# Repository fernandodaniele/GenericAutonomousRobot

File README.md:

# GenericAutonomousRobot (GAR)

Robot móvil diferencial desarrollado por el Grupo 1 para Técnicas Digitales III (TDIII) y Medidas Electrónicas II (MEII). La STM32 controla el movimiento, adquiere los sensores y ejecuta Safety y la navegación. La ESP32 sirve una interfaz web local para operar el robot y consultar su telemetría.

- Control manual, STOP y rearme explícito, con supervisión de proximidad, ausencia de piso y validez de sensores.
- Navegación autónoma supervisada con exploración local, odometría de encoders y maniobras acotadas.
- Panel web sin Internet, con estado, sensores, calibración manual del giroscopio y mapa 2D de ocupación posible.
- Registro de eventos en microSD. Funcionó en pruebas anteriores y requiere una nueva comprobación física por inconvenientes recientes del módulo.

La [arquitectura del sistema](Docs/ARCHITECTURE.md) describe tareas, interfaces, perfiles de navegación y límites de cada subsistema.

## Hardware

| Elemento | Configuración |
|---|---|
| Control | STM32F407G-DISC1, Cortex-M4 a 168 MHz, FreeRTOS |
| Comunicaciones | ESP32 clásico, objetivo `esp32dev` en PlatformIO con ESP-IDF |
| Tracción | Dos motores DC N20 con encoders, driver TB6612FNG |
| Sensores | Dos HC-SR04, frontal y trasero, cuatro TCRT5000 para detectar ausencia de piso y un MPU6050 |
| Registro | microSD por SPI y RTC DS1302 |
| Alimentación del prototipo | Batería LiPo 2S, 7,4 V nominales |

## Repositorio

| Ruta | Contenido |
|---|---|
| [Firmware/stm32_control](Firmware/stm32_control) | Firmware de control, Makefile y pruebas nativas |
| [Firmware/esp32_gateway](Firmware/esp32_gateway) | Firmware de comunicaciones, recursos web embebidos y pruebas |
| [Docs](Docs) | Arquitectura, diagramas del informe y convenciones |
| [Docs/Pruebas](Docs/Pruebas) | Procedimientos y resultados documentados por etapa |
| [Hardware](Hardware) | Lista de componentes y proyecto KiCad |

Abrir [PCB_Robot_Autonomo.kicad_pro](Hardware/PCB_Robot_Autonomo/PCB_Robot_Autonomo.kicad_pro) desde el gestor de KiCad 10. Mantener la estructura de la carpeta para que KiCad resuelva las tablas y modelos locales.

## Compilación y pruebas

Desde la raíz, con GNU Make y la toolchain ARM en el PATH para STM32, y PlatformIO para ESP32:

```sh
make -C Firmware/stm32_control -j4
pio run -d Firmware/esp32_gateway -e esp32
```

En Windows se puede usar `mingw32-make`. El entorno ESP32 fija la plataforma `espressif32 @ 6.12.0` y usa ESP-IDF 5.5.0. PlatformIO genera `firmware.elf` y `firmware.bin` en `Firmware/esp32_gateway/.pio/build/esp32/`. La aplicación debe caber en la partición factory de 1 MiB.

Las siguientes pruebas locales usan GCC nativo y Python 3 para Safety y arranque UART, y Node.js para JavaScript:

```powershell
.\Firmware\stm32_control\Tests\safety_b11\run.bat
.\Firmware\stm32_control\Tests\ultrasound\run.bat
powershell -ExecutionPolicy Bypass -File Firmware/esp32_gateway/Tests/w2/run.ps1
node Firmware/esp32_gateway/Tests/w2/run_js.js
```

Los runners, las fuentes de prueba y los mocks están en [Tests de STM32](Firmware/stm32_control/Tests) y [Tests de ESP32](Firmware/esp32_gateway/Tests). STM32 también dispone de runners para sensores, odometría e IMU. El [workflow de GitHub Actions](.github/workflows/main_ci.yml) compila ambos firmwares en pushes a `master` y pull requests dirigidos a `master`. Las regresiones anteriores se ejecutan por separado.

Para programar ambas placas, consultar el [procedimiento de grabación del firmware](Docs/Pruebas/AUTO3_GIRO_SUPERVISADO.md#programacion-y-validacion-posteriores-requieren-revision-previa).

## Uso y límites

Conectarse a la red local `GenericRobot` y abrir la dirección IP del punto de acceso. El panel distingue la disponibilidad del servidor ESP32 de la comunicación con STM32. Iniciar la exploración requiere una solicitud explícita y supervisión presencial.

La pose es relativa y usa parámetros geométricos provisionales. El mapa estima zonas observadas y posibles obstáculos a partir de ecos y odometría, sin SLAM ni cierre de bucle. Los HC-SR04 no cubren todo el espacio lateral durante un giro, y la falta de eco se trata como dato inválido. Si el teléfono pierde la conexión, STOP remoto puede quedar inaccesible.

## Créditos y licencia

Proyecto académico del Grupo 1. El código del proyecto se distribuye bajo la [licencia MIT](LICENSE), copyright 2026 fernandodaniele. Las bibliotecas incorporadas conservan sus avisos y licencias.

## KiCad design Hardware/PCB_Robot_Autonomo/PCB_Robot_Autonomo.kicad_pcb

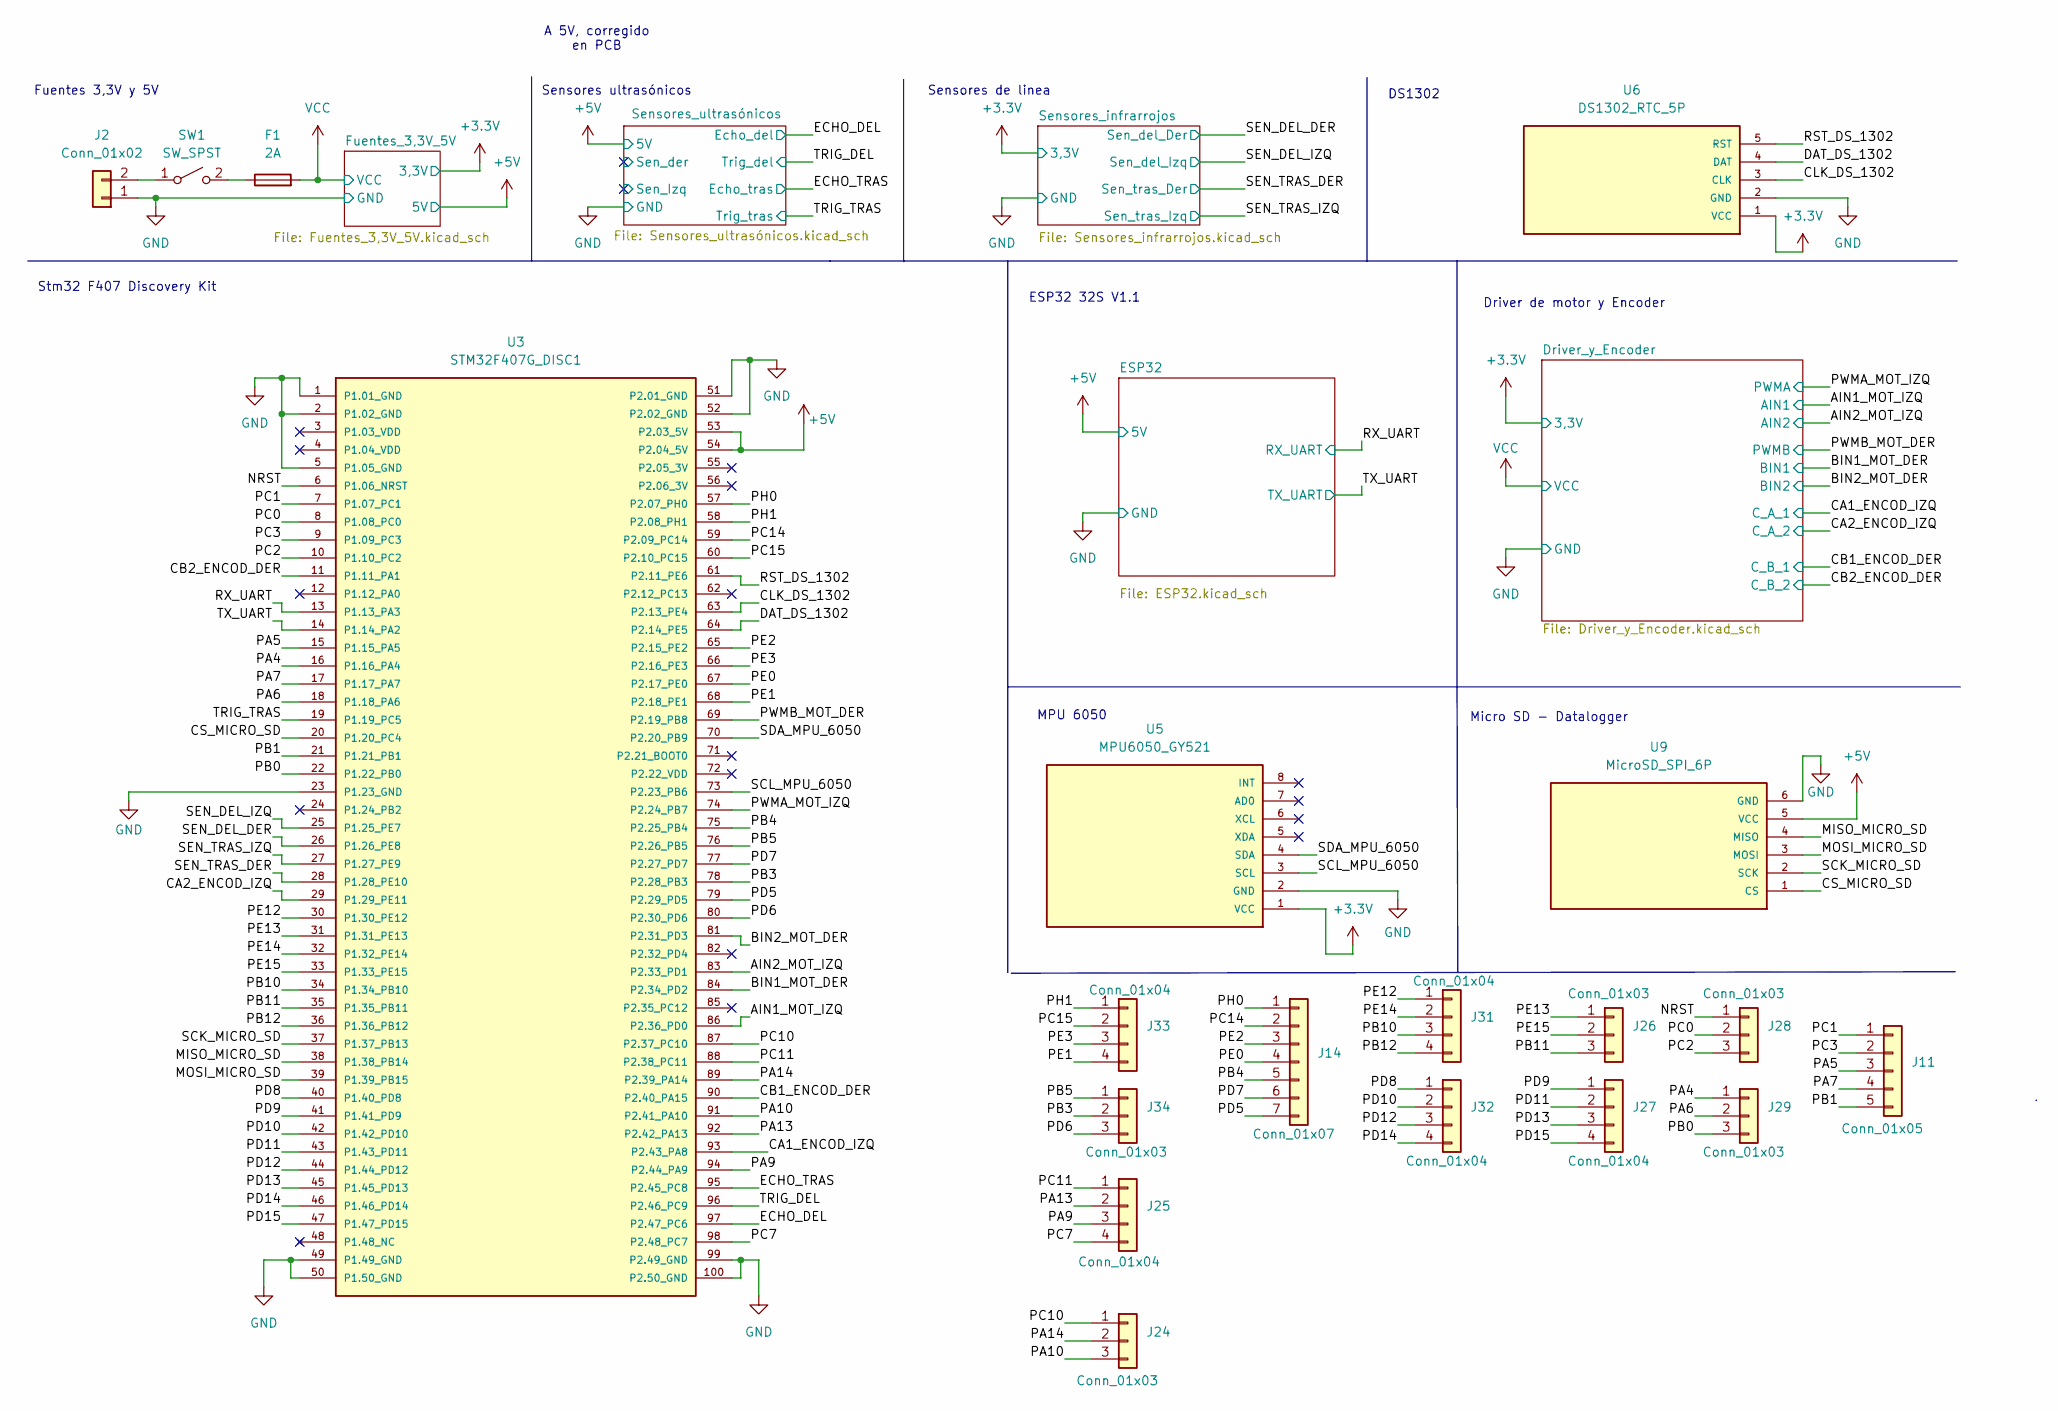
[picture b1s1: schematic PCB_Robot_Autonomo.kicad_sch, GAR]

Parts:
F1: 2A; Fuseholder_Cylinder-5x20mm_Schurter_0031_8201_Horizontal_Op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
J2: Conn_01x02; PinSocket_1x02_P2.54mm_Vertical
J11: Conn_01x05; PinSocket_1x05_P2.54mm_Vertical
J14: Conn_01x07; PinHeader_1x07_P2.54mm_Vertical
J24: Conn_01x03; PinHeader_1x03_P2.54mm_Vertical
J25, J27, J31, J32, J33: Conn_01x04; PinSocket_1x04_P2.54mm_Vertical
J26, J28, J29, J34: Conn_01x03; PinSocket_1x03_P2.54mm_Vertical
SW1: SW_SPST; SW_MTS102_A2_PCB_P4.70mm
U3: STM32F407G_DISC1
U5: MPU6050_GY521
U6: DS1302_RTC_5P
U9: MicroSD_SPI_6P

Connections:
+3.3V: U5.1 (VCC), U6.1 (VCC); also elsewhere on the board
+5V: U3.53 (P2.03_5V), U3.54 (P2.04_5V), U9.5 (VCC); also elsewhere on the board
/AIN1_MOT_IZQ: U3.86 (P2.36_PD0); also elsewhere on the board
/AIN2_MOT_IZQ: U3.83 (P2.33_PD1); also elsewhere on the board
/BIN1_MOT_DER: U3.84 (P2.34_PD2); also elsewhere on the board
/BIN2_MOT_DER: U3.81 (P2.31_PD3); also elsewhere on the board
/CA1_ENCOD_IZQ: U3.93 (P2.43_PA8); also elsewhere on the board
/CA2_ENCOD_IZQ: U3.29 (P1.29_PE11); also elsewhere on the board
/CB1_ENCOD_DER: U3.90 (P2.40_PA15); also elsewhere on the board
/CB2_ENCOD_DER: U3.11 (P1.11_PA1); also elsewhere on the board
/CLK_DS_1302: U3.63 (P2.13_PE4), U6.3 (CLK)
/CS_MICRO_SD: U3.20 (P1.20_PC4), U9.1 (CS)
/DAT_DS_1302: U3.64 (P2.14_PE5), U6.4 (DAT)
/ECHO_DEL: U3.97 (P2.47_PC6); also elsewhere on the board
/ECHO_TRAS: U3.95 (P2.45_PC8); also elsewhere on the board
/MISO_MICRO_SD: U3.38 (P1.38_PB14), U9.4 (MISO)
/MOSI_MICRO_SD: U3.39 (P1.39_PB15), U9.3 (MOSI)
/NRST: J28.1, U3.6 (P1.06_NRST)
/PA4: J29.1, U3.16 (P1.16_PA4)
/PA5: J11.3, U3.15 (P1.15_PA5)
/PA6: J29.2, U3.18 (P1.18_PA6)
/PA7: J11.4, U3.17 (P1.17_PA7)
/PA9: J25.3, U3.94 (P2.44_PA9)
/PA10: J24.3, U3.91 (P2.41_PA10)
/PA13: J25.2, U3.92 (P2.42_PA13)
/PA14: J24.2, U3.89 (P2.39_PA14)
/PB0: J29.3, U3.22 (P1.22_PB0)
/PB1: J11.5, U3.21 (P1.21_PB1)
/PB3: J34.2, U3.78 (P2.28_PB3)
/PB4: J14.5, U3.75 (P2.25_PB4)
/PB5: J34.1, U3.76 (P2.26_PB5)
/PB10: J31.3, U3.34 (P1.34_PB10)
/PB11: J26.3, U3.35 (P1.35_PB11)
/PB12: J31.4, U3.36 (P1.36_PB12)
/PC0: J28.2, U3.8 (P1.08_PC0)
/PC1: J11.1, U3.7 (P1.07_PC1)
/PC2: J28.3, U3.10 (P1.10_PC2)
/PC3: J11.2, U3.9 (P1.09_PC3)
/PC7: J25.4, U3.98 (P2.48_PC7)
/PC10: J24.1, U3.87 (P2.37_PC10)
/PC11: J25.1, U3.88 (P2.38_PC11)
/PC14: J14.2, U3.59 (P2.09_PC14)
/PC15: J33.2, U3.60 (P2.10_PC15)
/PD5: J14.7, U3.79 (P2.29_PD5)
/PD6: J34.3, U3.80 (P2.30_PD6)
/PD7: J14.6, U3.77 (P2.27_PD7)
/PD8: J32.1, U3.40 (P1.40_PD8)
/PD9: J27.1, U3.41 (P1.41_PD9)
/PD10: J32.2, U3.42 (P1.42_PD10)
/PD11: J27.2, U3.43 (P1.43_PD11)
/PD12: J32.3, U3.44 (P1.44_PD12)
/PD13: J27.3, U3.45 (P1.45_PD13)
/PD14: J32.4, U3.46 (P1.46_PD14)
/PD15: J27.4, U3.47 (P1.47_PD15)
/PE0: J14.4, U3.67 (P2.17_PE0)
/PE1: J33.4, U3.68 (P2.18_PE1)
/PE2: J14.3, U3.65 (P2.15_PE2)
/PE3: J33.3, U3.66 (P2.16_PE3)
/PE12: J31.1, U3.30 (P1.30_PE12)
/PE13: J26.1, U3.31 (P1.31_PE13)
/PE14: J31.2, U3.32 (P1.32_PE14)
/PE15: J26.2, U3.33 (P1.33_PE15)
/PH0: J14.1, U3.57 (P2.07_PH0)
/PH1: J33.1, U3.58 (P2.08_PH1)
/PWMA_MOT_IZQ: U3.74 (P2.24_PB7); also elsewhere on the board
/PWMB_MOT_DER: U3.69 (P2.19_PB8); also elsewhere on the board
/RST_DS_1302: U3.61 (P2.11_PE6), U6.5 (RST)
/RX_UART: U3.13 (P1.13_PA3); also elsewhere on the board
/SCK_MICRO_SD: U3.37 (P1.37_PB13), U9.2 (SCK)
/SCL_MPU_6050: U3.73 (P2.23_PB6), U5.3 (SCL)
/SDA_MPU_6050: U3.70 (P2.20_PB9), U5.4 (SDA)
/SEN_DEL_DER: U3.26 (P1.26_PE8); also elsewhere on the board
/SEN_DEL_IZQ: U3.25 (P1.25_PE7); also elsewhere on the board
/SEN_TRAS_DER: U3.28 (P1.28_PE10); also elsewhere on the board
/SEN_TRAS_IZQ: U3.27 (P1.27_PE9); also elsewhere on the board
/TRIG_DEL: U3.96 (P2.46_PC9); also elsewhere on the board
/TRIG_TRAS: U3.19 (P1.19_PC5); also elsewhere on the board
/TX_UART: U3.14 (P1.14_PA2); also elsewhere on the board
GND: J2.1, U3.1 (P1.01_GND), U3.2 (P1.02_GND), U3.5 (P1.05_GND), U3.23 (P1.23_GND), U3.49 (P1.49_GND), U3.50 (P1.50_GND), U3.51 (P2.01_GND), U3.52 (P2.02_GND), U3.99 (P2.49_GND), U3.100 (P2.50_GND), U5.2 (GND), U6.2 (GND), U9.6 (GND); also elsewhere on the board
unnamed: J2.2, SW1.1 (A)
unnamed: F1.1, SW1.2 (B)
VCC: F1.2; also elsewhere on the board

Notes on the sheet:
Stm32 F407 Discovery Kit
Fuentes 3,3V y 5V
A 5V, corregido en PCB
MPU 6050
DS1302
ESP32 32S V1.1
Sensores de linea
Micro SD - Datalogger
Sensores ultrasónicos
Driver de motor y Encoder

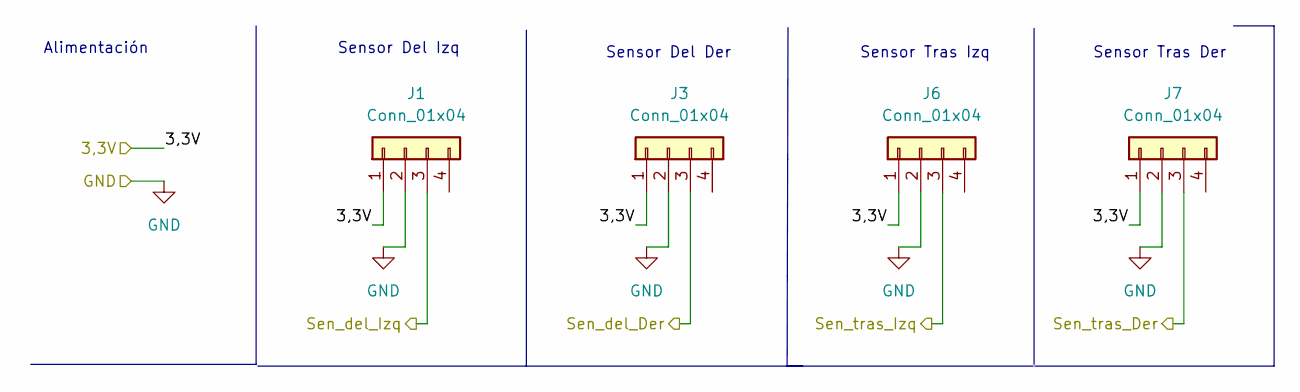
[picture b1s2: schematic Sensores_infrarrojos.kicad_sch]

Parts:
J1: Conn_01x04; PinSocket_1x04_P2.54mm_Vertical
J3, J6, J7: Conn_01x04; PinHeader_1x04_P2.54mm_Vertical

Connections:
+3.3V: J1.1, J3.1, J6.1, J7.1; also elsewhere on the board
/SEN_DEL_DER: J3.3; also elsewhere on the board
/SEN_DEL_IZQ: J1.3; also elsewhere on the board
/SEN_TRAS_DER: J7.3; also elsewhere on the board
/SEN_TRAS_IZQ: J6.3; also elsewhere on the board
GND: J1.2, J3.2, J6.2, J7.2; also elsewhere on the board

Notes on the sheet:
Sensor Tras Der
Sensor Tras Izq
Sensor Del Izq
Sensor Del Der
Alimentación

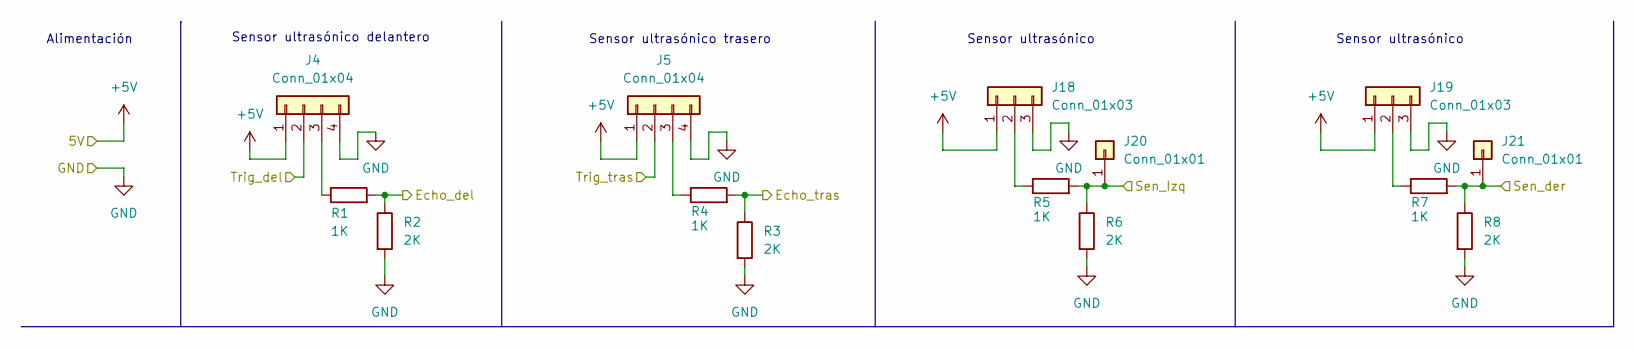
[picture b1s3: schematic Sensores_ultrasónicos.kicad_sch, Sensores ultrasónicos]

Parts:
J4, J5: Conn_01x04; PinHeader_1x04_P2.54mm_Vertical
J18, J19: Conn_01x03; PinHeader_1x03_P2.54mm_Vertical
J20, J21: Conn_01x01; PinHeader_1x01_P2.54mm_Vertical
R1, R4, R5, R7: 1K; R_Axial_DIN0207_L6.3mm_D2.5mm_P10.16mm_Horizontal
R2, R3, R6, R8: 2K; R_Axial_DIN0207_L6.3mm_D2.5mm_P10.16mm_Horizontal

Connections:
+3.3V: J4.1, J5.1, J18.1, J19.1; also elsewhere on the board
/ECHO_DEL: R1.2, R2.1; also elsewhere on the board
/ECHO_TRAS: R3.1, R4.2; also elsewhere on the board
/Sensores_ultrasónicos/Sen_Izq: J20.1 (Pin_1_1), R5.2, R6.1
/Sensores_ultrasónicos/Sen_der: J21.1 (Pin_1_1), R7.2, R8.1
/TRIG_DEL: J4.2; also elsewhere on the board
/TRIG_TRAS: J5.2; also elsewhere on the board
GND: J4.4, J5.4, J18.3, J19.3, R2.2, R3.2, R6.2, R8.2; also elsewhere on the board
unnamed: J4.3, R1.1
unnamed: J5.3, R4.1
unnamed: J18.2, R5.1
unnamed: J19.2, R7.1

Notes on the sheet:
Sensor ultrasónico
Sensor ultrasónico delantero
Sensor ultrasónico trasero
Alimentación
Sensor ultrasónico

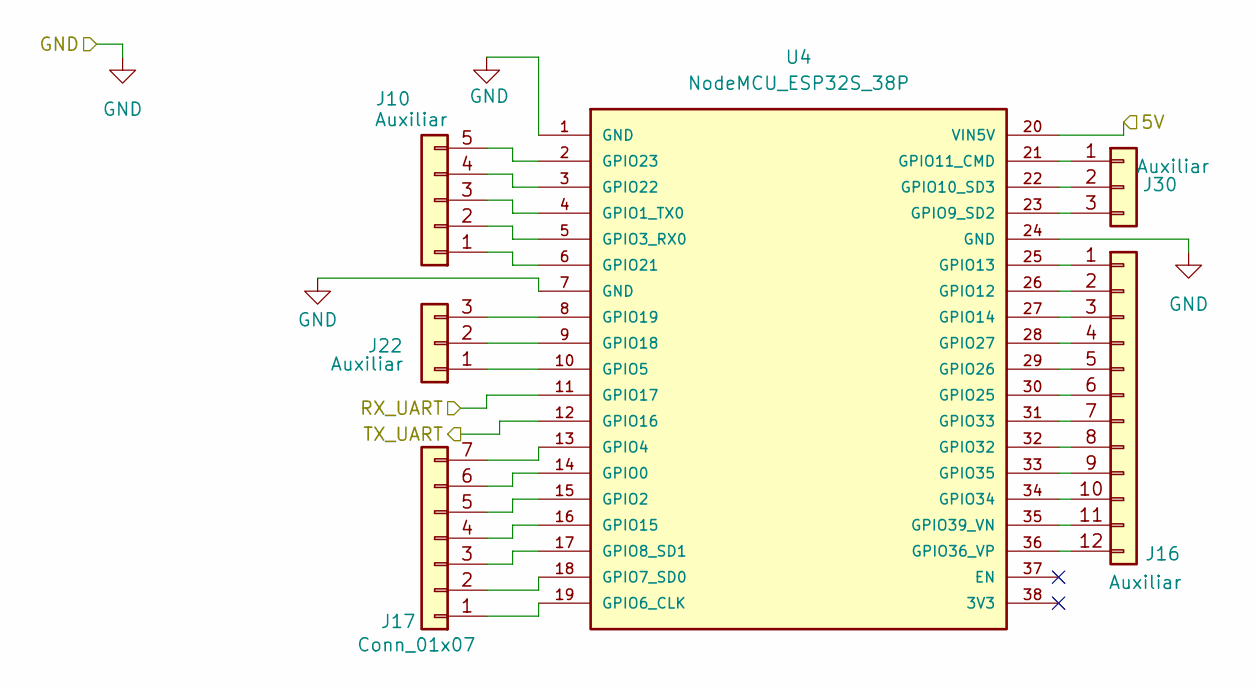
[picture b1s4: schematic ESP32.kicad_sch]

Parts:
J10: Auxiliar; PinHeader_1x05_P2.54mm_Vertical
J16: Auxiliar; PinHeader_1x12_P2.54mm_Vertical
J17: Conn_01x07; PinHeader_1x07_P2.54mm_Vertical
J22, J30: Auxiliar; PinHeader_1x03_P2.54mm_Vertical
U4: NodeMCU_ESP32S_38P

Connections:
+5V: U4.20 (VIN5V); also elsewhere on the board
/RX_UART: U4.11 (GPIO17); also elsewhere on the board
/TX_UART: U4.12 (GPIO16); also elsewhere on the board
GND: U4.1 (GND), U4.7 (GND), U4.24 (GND); also elsewhere on the board
unnamed: J10.1, U4.6 (GPIO21)
unnamed: J10.2, U4.5 (GPIO3_RX0)
unnamed: J10.3, U4.4 (GPIO1_TX0)
unnamed: J10.4, U4.3 (GPIO22)
unnamed: J10.5, U4.2 (GPIO23)
unnamed: J16.1, U4.25 (GPIO13)
unnamed: J16.2, U4.26 (GPIO12)
unnamed: J16.3, U4.27 (GPIO14)
unnamed: J16.4, U4.28 (GPIO27)
unnamed: J16.5, U4.29 (GPIO26)
unnamed: J16.6, U4.30 (GPIO25)
unnamed: J16.7, U4.31 (GPIO33)
unnamed: J16.8, U4.32 (GPIO32)
unnamed: J16.9, U4.33 (GPIO35)
unnamed: J16.10, U4.34 (GPIO34)
unnamed: J16.11, U4.35 (GPIO39_VN)
unnamed: J16.12, U4.36 (GPIO36_VP)
unnamed: J17.1, U4.19 (GPIO6_CLK)
unnamed: J17.2, U4.18 (GPIO7_SD0)
unnamed: J17.3, U4.17 (GPIO8_SD1)
unnamed: J17.4, U4.16 (GPIO15)
unnamed: J17.5, U4.15 (GPIO2)
unnamed: J17.6, U4.14 (GPIO0)
unnamed: J17.7, U4.13 (GPIO4)
unnamed: J22.1, U4.10 (GPIO5)
unnamed: J22.2, U4.9 (GPIO18)
unnamed: J22.3, U4.8 (GPIO19)
unnamed: J30.1, U4.21 (GPIO11_CMD)
unnamed: J30.2, U4.22 (GPIO10_SD3)
unnamed: J30.3, U4.23 (GPIO9_SD2)

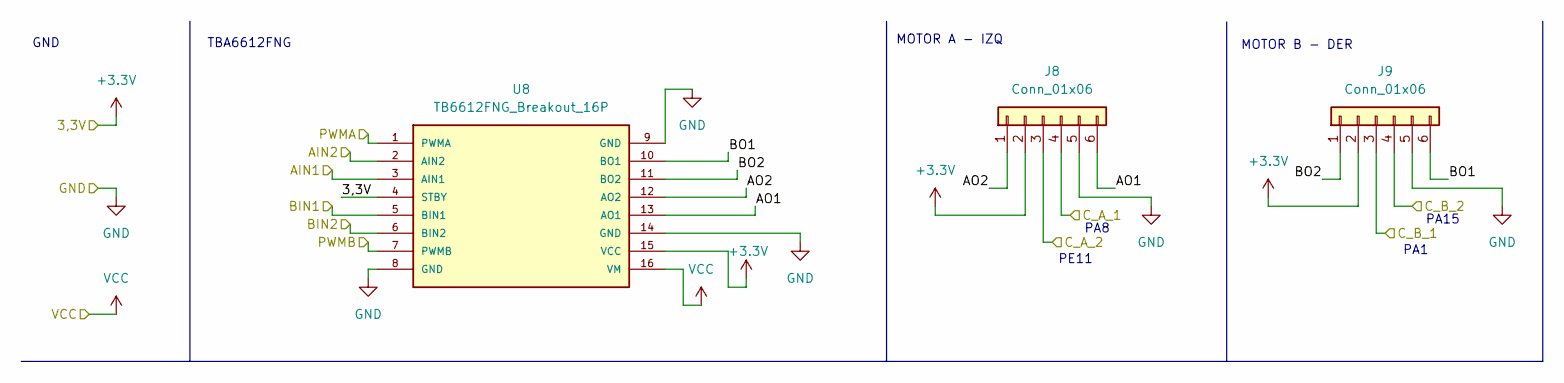
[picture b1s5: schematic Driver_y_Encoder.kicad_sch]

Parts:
J8, J9: Conn_01x06; PinHeader_1x06_P2.54mm_Vertical
U8: TB6612FNG_Breakout_16P

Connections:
+3.3V: J8.2, J9.2, U8.4 (STBY), U8.15 (VCC); also elsewhere on the board
/AIN1_MOT_IZQ: U8.3 (AIN1); also elsewhere on the board
/AIN2_MOT_IZQ: U8.2 (AIN2); also elsewhere on the board
/BIN1_MOT_DER: U8.5 (BIN1); also elsewhere on the board
/BIN2_MOT_DER: U8.6 (BIN2); also elsewhere on the board
/CA1_ENCOD_IZQ: J8.4; also elsewhere on the board
/CA2_ENCOD_IZQ: J8.3; also elsewhere on the board
/CB1_ENCOD_DER: J9.3; also elsewhere on the board
/CB2_ENCOD_DER: J9.4; also elsewhere on the board
/Driver_y_Encoder/AO1: J8.6, U8.13 (AO1)
/Driver_y_Encoder/AO2: J8.1, U8.12 (AO2)
/Driver_y_Encoder/BO1: J9.6, U8.10 (BO1)
/Driver_y_Encoder/BO2: J9.1, U8.11 (BO2)
/PWMA_MOT_IZQ: U8.1 (PWMA); also elsewhere on the board
/PWMB_MOT_DER: U8.7 (PWMB); also elsewhere on the board
GND: J8.5, J9.5, U8.8 (GND), U8.9 (GND), U8.14 (GND); also elsewhere on the board
VCC: U8.16 (VM); also elsewhere on the board

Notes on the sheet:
MOTOR A - IZQ
MOTOR B - DER
PA15
PA1
PA8
GND
PE11
TBA6612FNG

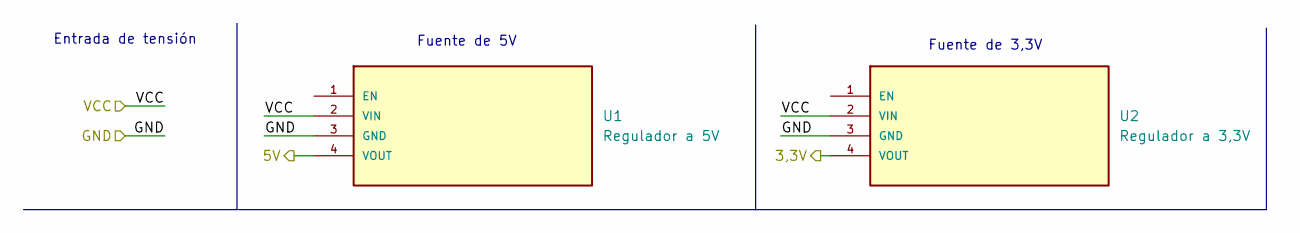
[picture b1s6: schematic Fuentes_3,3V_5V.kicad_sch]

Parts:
U1: Regulador a 5V; StepDown_Mini_3A_0V8_17V
U2: Regulador a 3,3V; StepDown_Mini_3A_0V8_17V

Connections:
+3.3V: U2.4 (VOUT); also elsewhere on the board
+5V: U1.4 (VOUT); also elsewhere on the board
GND: U1.3 (GND), U2.3 (GND); also elsewhere on the board
VCC: U1.2 (VIN), U2.2 (VIN); also elsewhere on the board

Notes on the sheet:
Fuente de 5V
Fuente de 3,3V
Entrada de tensión

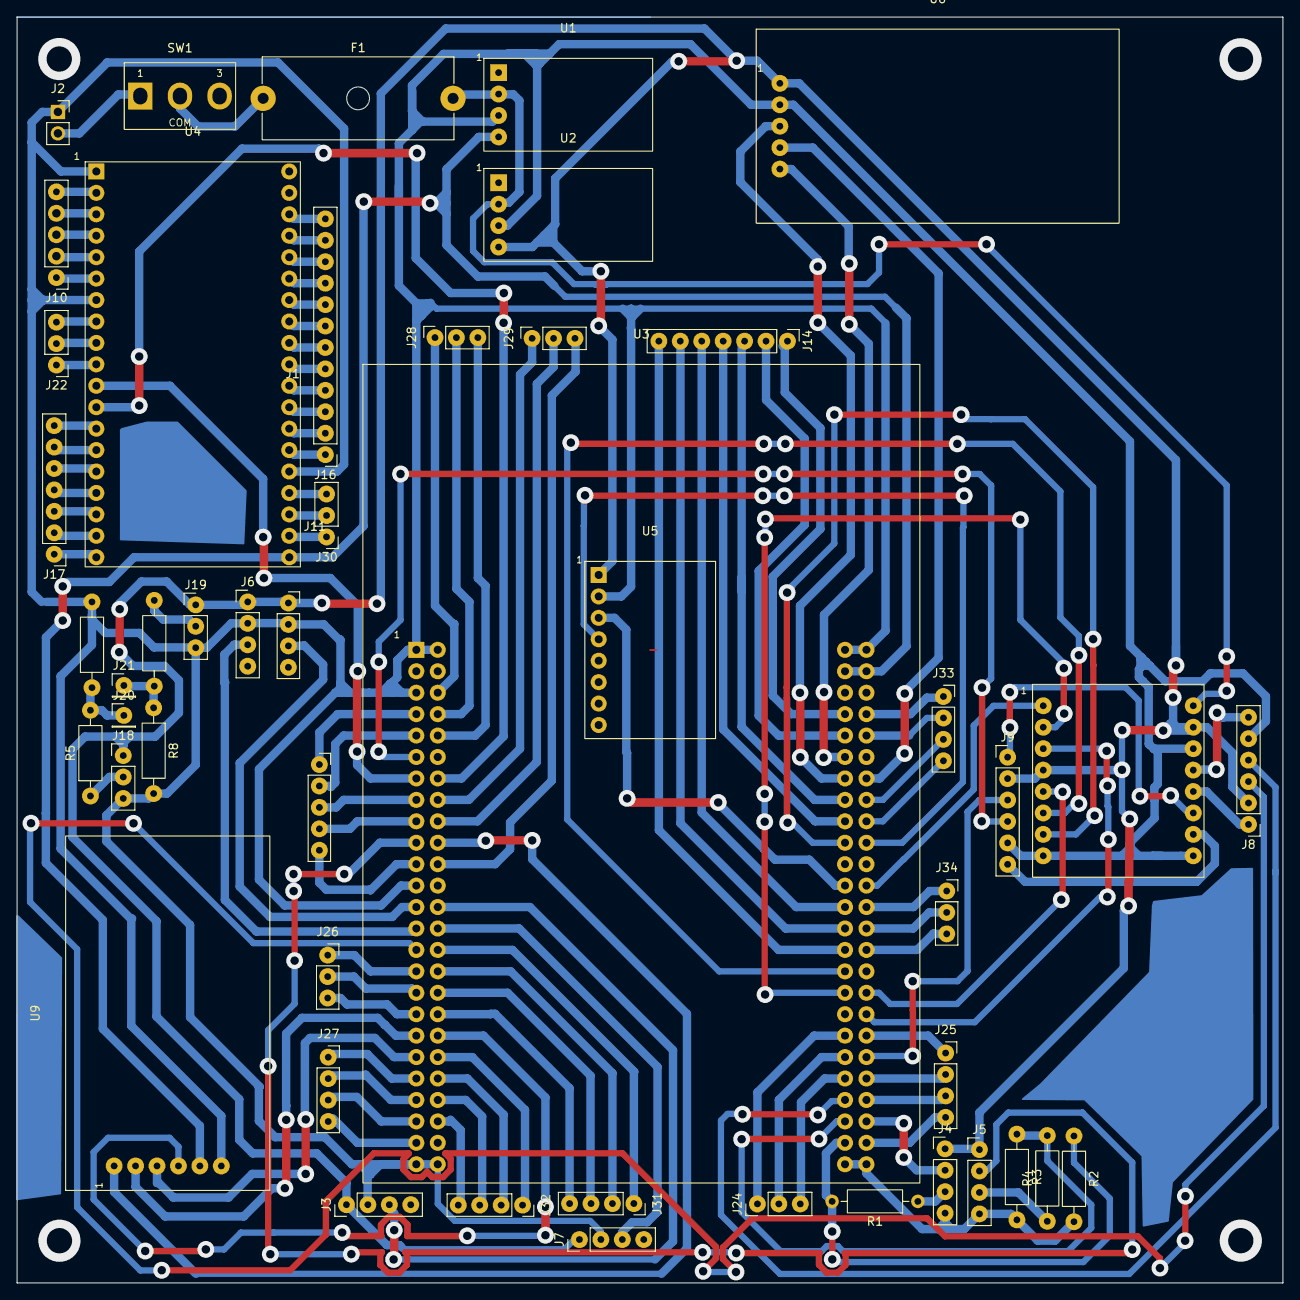
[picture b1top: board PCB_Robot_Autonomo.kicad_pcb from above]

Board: 2 copper layers, 150.0 x 150.0 mm, 48 parts (0 on the bottom side), 122 nets.

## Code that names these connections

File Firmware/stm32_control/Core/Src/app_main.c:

/**
 * @file    app_main.c
 * @brief   Punto de entrada de la aplicación (int main).
 *
 * STM32CubeMX (projectgenerator 4.7.0-B52) NO genera la función main() para
 * este proyecto: su Core/Src/main.c sale SIN main() en cada "Generate Code"
 * (probado 3 veces, incluso borrando main.c antes de regenerar).
 *
 * Por eso main() vive acá, en un archivo que CubeMX no conoce ni toca (se
 * compila vía GNUmakefile -> APP_C_SOURCES). El Core/Src/main.c de CubeMX
 * queda solo con SystemClock_Config / Error_Handler / assert_failed, que sí
 * regenera bien. Un "Generate Code" puede reescribir main.c sin romper nada.
 *
 * Ver fix-plan.md §5.
 */

#include "main.h"
#include "cmsis_os.h"
#include "i2c.h"
#include "spi.h"
#include "tim.h"
#include "usart.h"
#include "usb_device.h"
#include "gpio.h"

#include "fatfs.h"
#include "drv_motor.h"
#include "drv_ultrasound.h"
#include "mid_kinematics.h"
#include "ds1302.h"
#include "mid_log.h"
#include "drv_uart.h"
#include <string.h>

/* Generadas por CubeMX en main.c / freertos.c */
extern void SystemClock_Config(void);
extern void MX_FREERTOS_Init(void);

/* Objetos de las capas de la aplicación (las tareas se crean en freertos.c). */
MotorHandle_t motor_l, motor_r;
RobotCommand_t robot_cmd;
DrvUart_t esp_uart;
char uart_message[UART_RX_BUFFER_SIZE];
Ds1302_t ds1302;

/**
  * @brief  The application entry point.
  * @retval int
  */
int main(void)
{
  HAL_Init();
  SystemClock_Config();

  /* Periféricos configurados por CubeMX */
  MX_GPIO_Init();
  MX_I2C1_Init();
  MX_SPI2_Init();
  MX_TIM2_Init();
  MX_TIM4_Init();
  MX_USART2_UART_Init();
  /* MX_USB_DEVICE_Init() lo llama StartDefaultTask (freertos.c), como genera CubeMX. */

  /* FatFs: enlaza el driver USER (drv_sd_spi). No está en el .ioc, ver FATFS/README.md. */
  MX_FATFS_Init();

  /* 1. UART hacia el ESP32 */
  DrvUart_Init(&esp_uart, &huart2);
  DrvUart_StartReceive(&esp_uart);
  DrvUart_SendString(&esp_uart, "STM32 UART ready\n");

  /* 2. Motores (TB6612FNG, PWM por TIM4) */
  motor_l.htim = &htim4;
  motor_l.channel = TIM_CHANNEL_2;
  motor_l.port_a = GPIOD; motor_l.pin_a = GPIO_PIN_0;
  motor_l.port_b = GPIOD; motor_l.pin_b = GPIO_PIN_1;
  Motor_Init(&motor_l);

  motor_r.htim = &htim4;
  motor_r.channel = TIM_CHANNEL_3;
  motor_r.port_a = GPIOD; motor_r.pin_a = GPIO_PIN_2;
  motor_r.port_b = GPIOD; motor_r.pin_b = GPIO_PIN_3;
  Motor_Init(&motor_r);

  /* 3. Ultrasonido HC-SR04: TRIG=PB4, ECHO=PA6 (TIM3_CH1 + DMA1_Stream4).
   *    El driver gestiona TIM3 y el DMA internamente. */
  HCSR04_Init();

  /* 4. RTC DS1302 (bit-bang: CLK=PD8, DAT=PD9, RST=PD10; GPIO en MX_GPIO_Init) */
  const Ds1302Config_t ds1302_cfg = {
      .reset_pin = { .mcu_port = DS1302_RST_GPIO_Port, .pin = DS1302_RST_Pin }
  };
  DS1302_Init(&ds1302, &ds1302_cfg);
  /* Bring-up: hora fija en cada arranque para validar el driver.
   * TODO: setear solo si el reloj no corre (bit CH) y tomar la hora real. */
  DS1302_SetTime(&ds1302,
                 0U,      /* formato 24 h            */
                 12U,     /* horas                   */
                 0U,      /* minutos                 */
                 0U,      /* segundos                */
                 0U,      /* am_pm (ignorado en 24h) */
                 1U,      /* dia de semana (1 = Dom)  */
                 1U,      /* dia del mes             */
                 1U,      /* mes (1 = Ene)           */
                 2026);   /* anio                    */

  /* 5. Logger por USB CDC + SD, con timestamp del DS1302. */
  Log_Init(&ds1302);

  /* Arranque de FreeRTOS (flujo nativo de CubeMX). */
  osKernelInitialize();
  MX_FREERTOS_Init();
  osKernelStart();

  /* No se llega acá: el scheduler tomó el control. */
  while (1)
  {
  }
}

/**
 * @brief Callback ejecutado cuando se completa la recepción UART por interrupción.
 * @param huart Puntero al handle UART que generó la interrupción.
 */
void HAL_UART_RxCpltCallback(UART_HandleTypeDef *huart)
{
  if (huart->Instance == USART2)
  {
    DrvUart_RxCallback(&esp_uart);
  }
}
